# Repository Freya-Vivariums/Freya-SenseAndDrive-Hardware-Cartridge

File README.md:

The **Sense'n'Drive Hardware Cartridge** equips the [Edgeberry™](https://edgeberry.github.io) based controller with the capability for connecting sensors and driving actuators.

**Features**
- **6 digital outputs** for driving actuators directly or with interposing relays, with internal or external power source.
- **An I²C port** level-shifted to 5V for reliably connecting to the [Freya "Terra" Sensor](https://github.com/Freya-Vivariums/Freya-Terra-Sensor)

<br clear="right"/>

## Usage

The Sense'n'Drive Hardware Cartridge is slided in into the expansion slot on the back side of the controller. For using it in your application, install the driver from this repository and include the sdk library in your software.

```js
const { SenseNDriveClient } = require('@freya-vivariums/freya-hardware-cartridge');

const cartridge = new SenseNDriveClient();

cartridge.on('ready', async () => {
  await cartridge.setOutput({ channel: 1, config: { mode: 'switch' }, setpoint: 1 });
  setTimeout(() => cartridge.setOutput({ channel: 1, setpoint: 0 }), 1000);
});
```

<br clear="left"/>

## Hardware

### Sensor Port
The I²C sensor port is **level-shifted to 5V**, and wired to the `HY2.0-4P` connector (informally known as the _Grove connector_) in the following way - making it directly compatible with a wide range of I²C breakout boards from a variety of ecosystems.

|  Pin   | Function |
|--------|----------|
| 1      | SCL      |
| 2      | SDA      |
| 3      | +5V      |
| 4      | GND      |

> [!NOTE]
> Before you can use the I²C port `/dev/i2c-1` on Raspberry Pi, it must be enabled by running`sudo raspi-config nonint do_i2c 0`. Or by configuring the overlay manually.

### Digital Outputs
The digital outputs are **sourcing MOSFET** channels rated for up to 1A each, suitable for driving standard industrial actuators such as relays, contactors and solenoids. Output voltage follows the externally applied supply. At 24V DC, the outputs conform to the conventional sourcing digital output arrangement described in IEC 61131-2, so any actuator designed for a standard PLC output can be connected directly. Built-in flyback diodes clamp inductive loads.

> [!IMPORTANT]
> **The digital outputs do not feature internal short-circuit or overcurrent protection**. It is recommended to install a 1A or 1.25A fast-acting fuse on the power supply line.

> [!WARNING]
> The hardware cartridge is designed with a **shared ground for all voltages (non-isolated)**. Always ensure the power supply for the digital outputs and the power supply for the device share a common ground.

The Raspberry Pi GPIO pins are connected to the digital outputs as following:

|Channel |  GPIO  | Software Driver Channel | Comment |
|--------|--------|-------------------------|---------|
| D1     | GPIO21 | 1       |                     |
| D2     | GPIO20 | 2       |                     |
| D3     | GPIO16 | 3       |                     |
| D4     | GPIO13 | 4       |                     |
| D5     | GPIO12 | 5       |Hardware PWM capable* |
| D6     | GPIO18 | 6       |Hardware PWM capable* |

> [!NOTE]
> TODO a note on Hardware PWM on Raspberry Pi

> [!NOTE]
> Controling the digital outputs can be done directly from the commandline using `pinctrl`. For example `pinctrl set 21 op dh` to use GPIO21 as a digital output and set high.

## Software
The **Sense'n'Drive Hardware Cartridge driver** included in the repository is a systemd service (`freya.cartridge.sensendrive`) that is interacted with via a D-Bus API by the client libraries. The service provides methods for controlling the digital outputs in several operating modes.

### D-Bus API
System bus service and interface `freya.cartridge.sensendrive`. Methods are `(s) → s`: a bare JSON request in,
an enveloped JSON response out.

| Method | Request | Result |
|---|---|---|
| `GetOutputs` | `{}` | `{ "outputs": [ ...6...] }` |
| `SetOutput` | one write document | the resulting state |
| `SetOutputs` | `{ "outputs": [ ... ] }` | array of states |

#### Example
`SetOutput` request argument string:
```json
{
  "channel": 2,
  "config": { "mode": "pulse", "frequency_hz": 0.1, "rampRate": 0 },
  "setpoint": 0.321
}
```
Response string:
```json
{ "ok": false, "error": { "code": "EINVAL", "message": "..." } }
```
Or
```json
{ "ok": true, "result": {
    "channel": 2,
    "config": { "mode": "pulse", "frequency_hz": 0.1, "rampRate": 0 },
    "setpoint": 0.321,
    "actual": 0.3 } }
```

Signals: `Ready` at startup, and `OutputChanged` carrying one state document
whenever a channel changes.

## License & Collaboration
**Copyright© 2024-2026 Sanne 'SpuQ' Santens**. The hardware and enclosure are released under the [**CERN OHL-W**](Hardware/LICENSE.txt) license. The driver is released under the [**GNU GPL-3.0**](Software/Driver/LICENSE.txt) license and the sdk libraries under the [**MIT license**](Software/Client/LICENSE.txt) Trademark rules apply to the [Freya™ brand](https://github.com/Freya-Vivariums/.github/blob/main/brand/Freya_Trademark_Rules_and_Guidelines.md).

### Collaboration

If you'd like to contribute to this project, please follow these guidelines:
1. Fork the repository and create your branch from `main`.
2. Make your changes and ensure they adhere to the project's design style and conventions.
3. Test your changes thoroughly.
4. Ensure your commits are descriptive and well-documented.
5. Open a pull request, describing the changes you've made and the problem or feature they address.

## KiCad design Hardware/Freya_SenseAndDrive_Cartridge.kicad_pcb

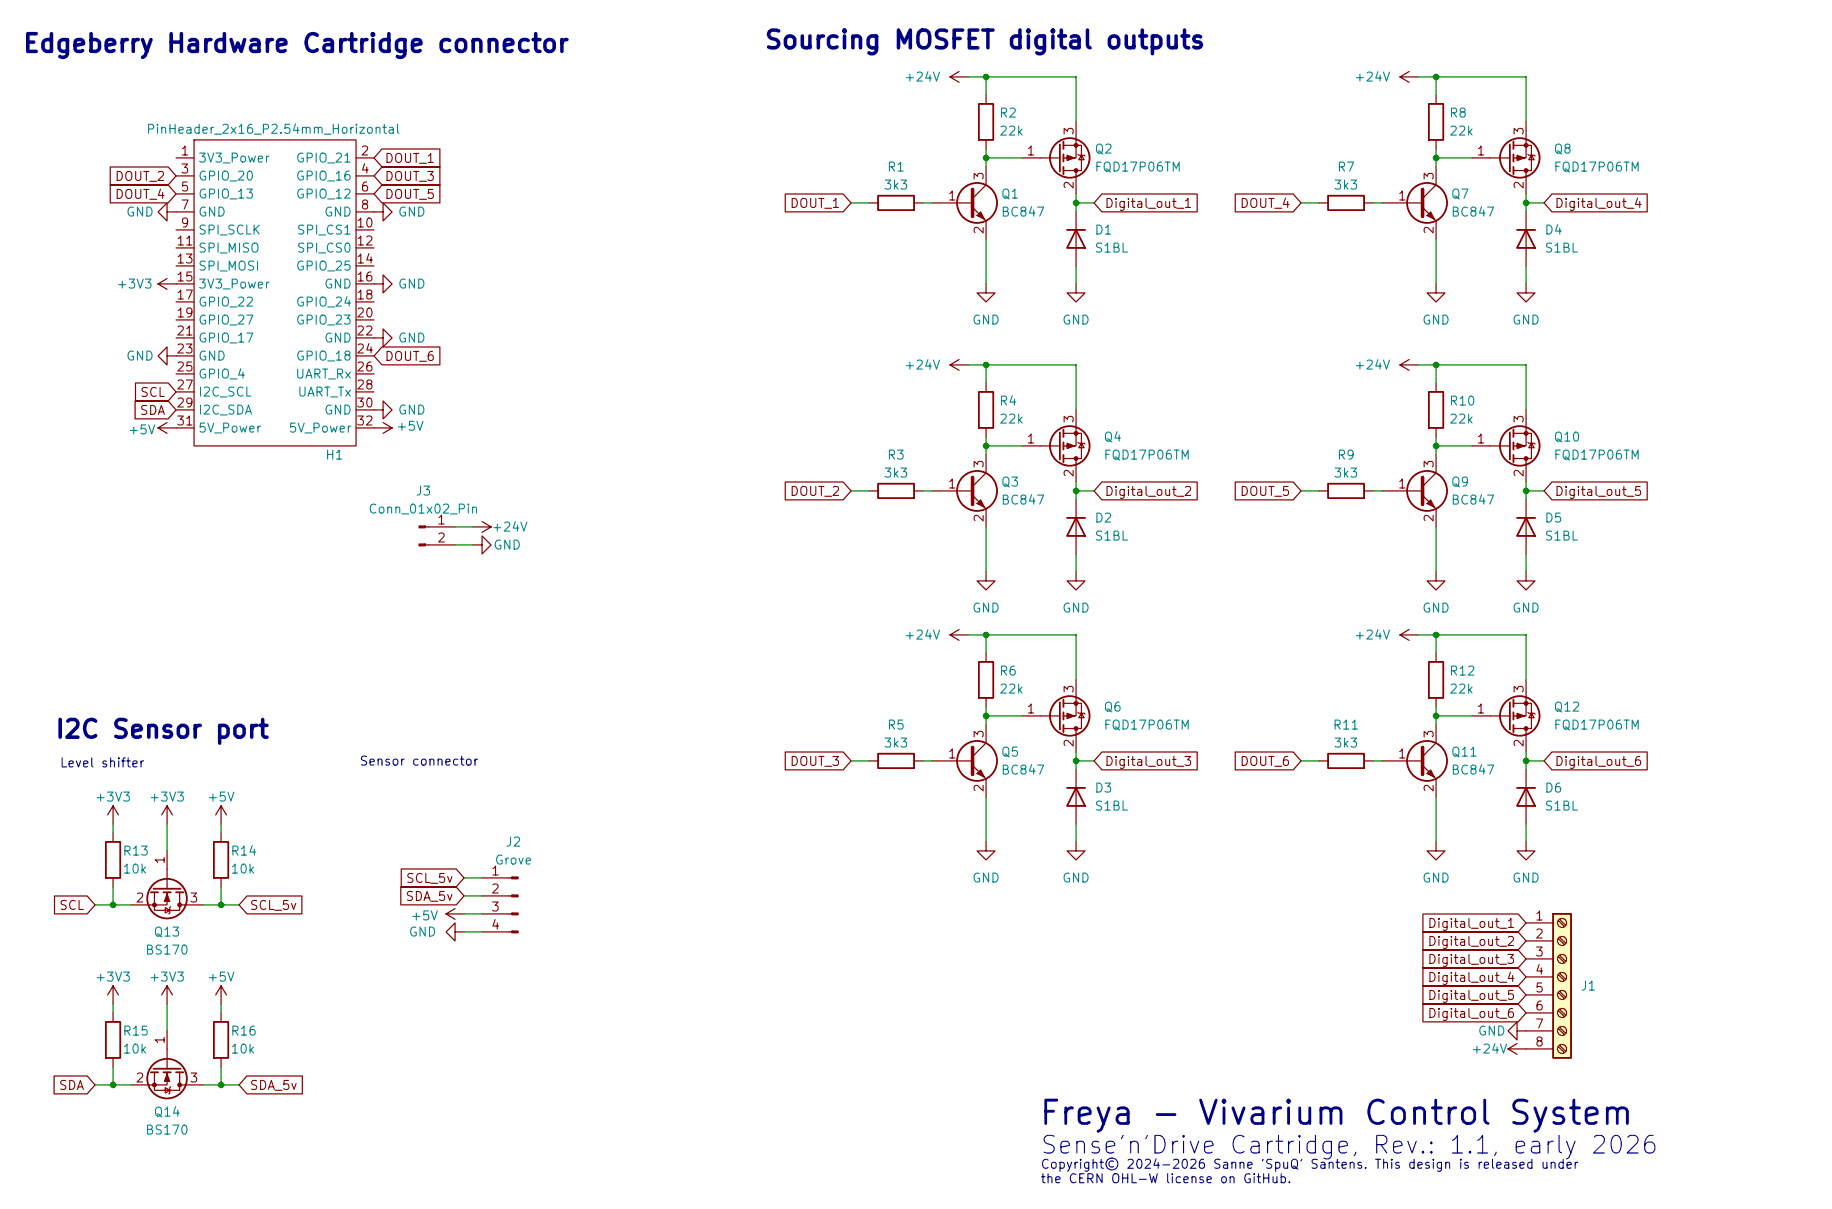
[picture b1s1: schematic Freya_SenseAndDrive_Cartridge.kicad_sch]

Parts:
D1, D2, D3, D4, D5, D6: S1BL; S1BL_diode
H1: PinHeader_2x16_P2.54mm_Horizontal
J1: Screw_Terminal_01x08; PhoenixContact_MSTBA_2,5_8-G-5,08_1x08_P5.08mm_Horizontal
J2: Grove; Grove_SMD_right_angle
J3: Conn_01x02_Pin; Molex_KK-254_AE-6410-02A_1x02_P2.54mm_Vertical
Q1, Q3, Q5, Q7, Q9, Q11: BC847; SOT-23
Q2, Q4, Q6, Q8, Q10, Q12: FQD17P06TM; TO-252-2
Q13, Q14: BS170; SOT-23
R1, R3, R5, R7, R9, R11: 3k3; R_0805_2012Metric
R2, R4, R6, R8, R10, R12: 22k; R_0805_2012Metric
R13, R14, R15, R16: 10k; R_0805_2012Metric

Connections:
+3V3: H1.15 (3V3_Power), Q13.1 (G), Q14.1 (G), R13.1, R15.1
+5V: H1.31 (5V_Power), H1.32 (5V_Power), J2.3, R14.1, R16.1
+24V: J1.8, J3.1, Q2.3 (S), Q4.3 (S), Q6.3 (S), Q8.3 (S), Q10.3 (S), Q12.3 (S), R2.1, R4.1, R6.1, R8.1, R10.1, R12.1
DOUT_1: H1.2 (GPIO_21), R1.1
DOUT_2: H1.3 (GPIO_20), R3.1
DOUT_3: H1.4 (GPIO_16), R5.1
DOUT_4: H1.5 (GPIO_13), R7.1
DOUT_5: H1.6 (GPIO_12), R9.1
DOUT_6: H1.24 (GPIO_18), R11.1
Digital_out_1: D1.1 (K), J1.1, Q2.2 (D)
Digital_out_2: D2.1 (K), J1.2, Q4.2 (D)
Digital_out_3: D3.1 (K), J1.3, Q6.2 (D)
Digital_out_4: D4.1 (K), J1.4, Q8.2 (D)
Digital_out_5: D5.1 (K), J1.5, Q10.2 (D)
Digital_out_6: D6.1 (K), J1.6, Q12.2 (D)
GND: D1.2 (A), D2.2 (A), D3.2 (A), D4.2 (A), D5.2 (A), D6.2 (A), H1.7 (GND), H1.8 (GND), H1.16 (GND), H1.22 (GND), H1.23 (GND), H1.30 (GND), J1.7, J2.4, J3.2, Q1.2 (E), Q3.2 (E), Q5.2 (E), Q7.2 (E), Q9.2 (E), Q11.2 (E)
unnamed: Q1.1 (B), R1.2
unnamed: Q1.3 (C), Q2.1 (G), R2.2
unnamed: Q3.1 (B), R3.2
unnamed: Q3.3 (C), Q4.1 (G), R4.2
unnamed: Q5.1 (B), R5.2
unnamed: Q5.3 (C), Q6.1 (G), R6.2
unnamed: Q7.1 (B), R7.2
unnamed: Q7.3 (C), Q8.1 (G), R8.2
unnamed: Q9.1 (B), R9.2
unnamed: Q9.3 (C), Q10.1 (G), R10.2
unnamed: Q11.1 (B), R11.2
unnamed: Q11.3 (C), Q12.1 (G), R12.2
SCL: H1.27 (I2C_SCL), Q13.2 (S), R13.2
SCL_5v: J2.1, Q13.3 (D), R14.2
SDA: H1.29 (I2C_SDA), Q14.2 (S), R15.2
SDA_5v: J2.2, Q14.3 (D), R16.2

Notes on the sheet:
Copyright© 2024-2026 Sanne 'SpuQ' Santens. This design is released under the CERN OHL-W license on GitHub.
I2C Sensor port
Freya - Vivarium Control System
Sense'n'Drive Cartridge, Rev.: 1.1, early 2026
Sourcing MOSFET digital outputs
Sensor connector
Level shifter
Edgeberry Hardware Cartridge connector

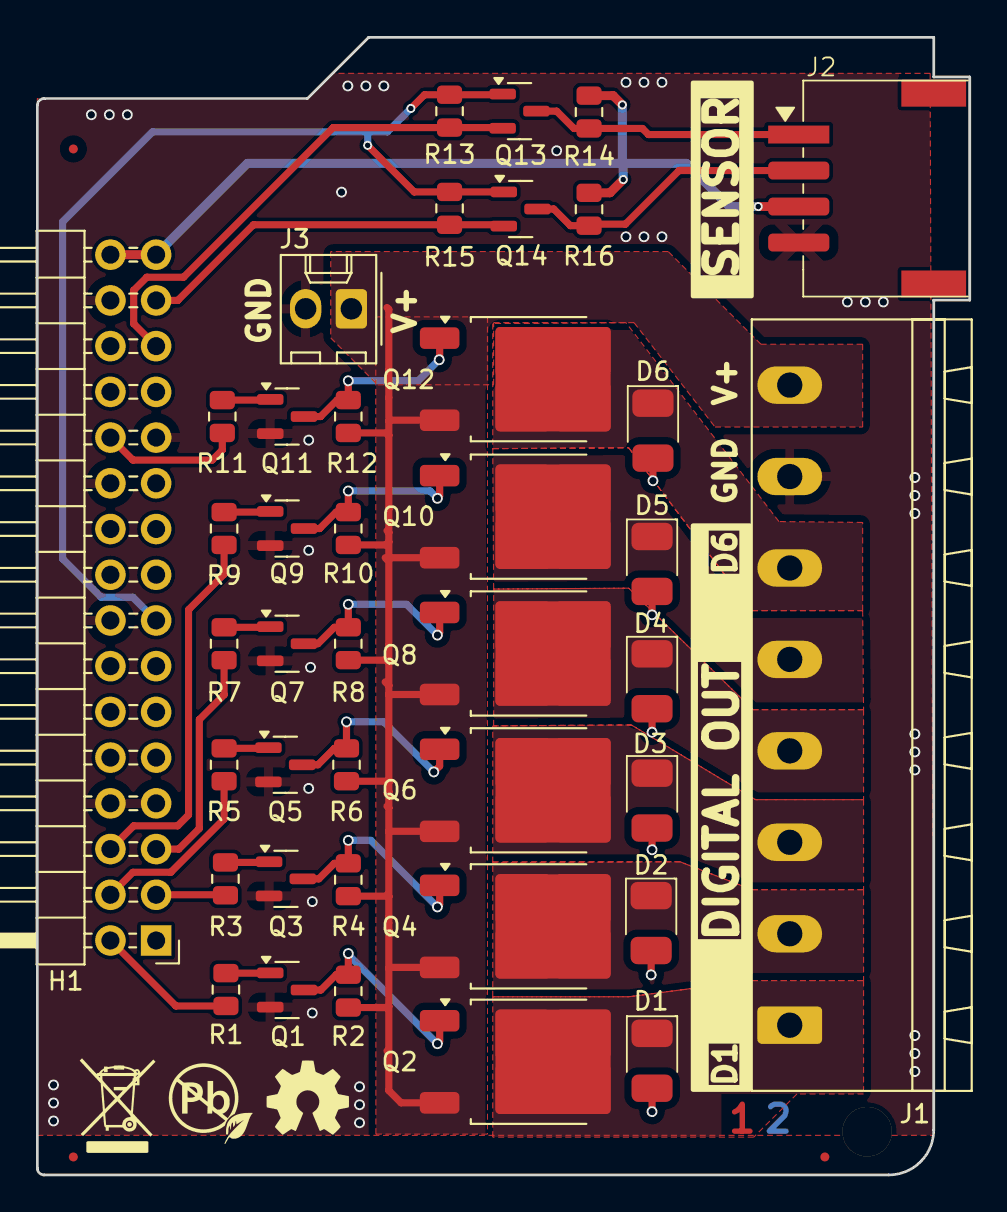
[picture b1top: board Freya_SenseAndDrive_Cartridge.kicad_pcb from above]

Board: 2 copper layers, 51.8 x 63.2 mm, 40 parts (0 on the bottom side), 32 nets.

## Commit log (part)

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2026-02-06 Project's structure adaptation
2026-02-06 ReadMe: tweaks to the wordings
2026-02-06 ReadMe: Trademark rules for Freya and Edgeberry
2026-02-06 Software migration to this repo
2026-02-06 Hardware: naming in project
2026-02-09 Repo organization: software driver + client
2026-02-09 Repo licenses
2026-04-16 Hardware: Enclosure update
2026-04-20 Documentation: cartridge usage
2026-04-21 ReadMe: usage documentation
2026-05-29 Software: Node library + Node-RED nodes
2026-05-29 Software: Node-RED nodes readme
2026-05-29 Software: Node-RED Digital Ouput Node rename
2026-05-29 Software: system & dbus service name update

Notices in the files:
Hardware/Freya_SenseAndDrive_Cartridge.kicad_pcb:
Copyright© 2024 Sanne 'SpuQ' Santens. This design is released under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
